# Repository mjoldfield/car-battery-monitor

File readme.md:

# Car battery monitor

My car tends to eat batteries! Sometimes, particularly during pandemic
summers many weeks pass without the car being used, and during this
time sometimes the battery discharges. I suspect the underlying
problem is that somewhere current is leaking to ground, but that seems
hard to fix. Instead, I’d be happy to just monitor the situation and
charge the battery if needed.

The car is usually parked in range of the home WiFi network, so a
convenient solution would be to have the car send me email about its
battery every once in while.

## code

All written in CircuitPython

## pcb

A PCB to hold tne TinyS2 and DC-DC converter boards, designed in KiCad.

## case

A 3D-printable case designed with OpenSCAD.

# Blog post

See [my blog](https://mjoldfield.com/atelier/2021/12/car-battery-monitor.html) for
more details.

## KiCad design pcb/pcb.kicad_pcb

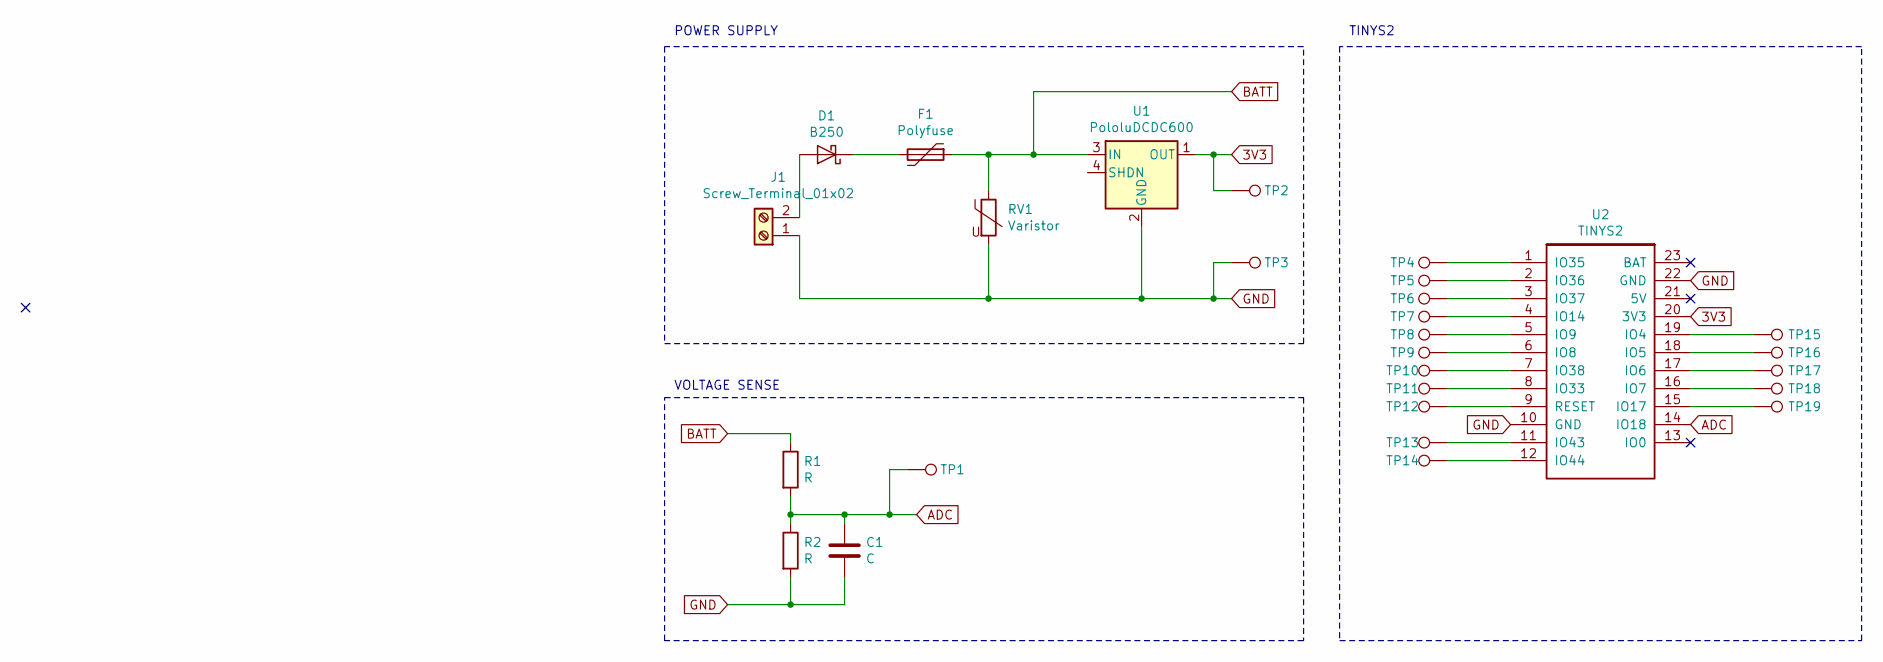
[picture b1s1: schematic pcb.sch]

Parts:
C1: C; C_0805_2012Metric_Pad1.15x1.40mm_HandSolder
D1: B250; D_SMB
F1: Polyfuse; C_1206_3216Metric_Pad1.42x1.75mm_HandSolder
J1: Screw_Terminal_01x02; TerminalBlock_bornier-2_P5.08mm
R1, R2: R; R_0805_2012Metric_Pad1.15x1.40mm_HandSolder
RV1: Varistor; C_1210_3225Metric_Pad1.42x2.65mm_HandSolder
TP1, TP2, TP3, TP4, TP5, TP6, TP7, TP8, TP9, TP10, TP11, TP12, TP13, TP14, TP15, TP16, TP17, TP18, TP19: TestPoint; TestPoint_THTPad_D2.0mm_Drill1.0mm
U1: PololuDCDC600; PololuDCDC4
U2: TINYS2

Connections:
3V3: TP2.1, U1.1 (OUT), U2.20 (3V3)
ADC: C1.1, R1.2, R2.1, TP1.1, U2.14 (IO18)
BATT: F1.1, R1.1, RV1.1, U1.3 (IN)
GND: C1.2, J1.1, R2.2, RV1.2, TP3.1, U1.2 (GND), U2.10 (GND), U2.22 (GND)
unnamed: D1.1 (K), F1.2
unnamed: D1.2 (A), J1.2
unnamed: TP4.1, U2.1 (IO35)
unnamed: TP5.1, U2.2 (IO36)
unnamed: TP6.1, U2.3 (IO37)
unnamed: TP7.1, U2.4 (IO14)
unnamed: TP8.1, U2.5 (IO9)
unnamed: TP9.1, U2.6 (IO8)
unnamed: TP10.1, U2.7 (IO38)
unnamed: TP11.1, U2.8 (IO33)
unnamed: TP12.1, U2.9 (RESET)
unnamed: TP13.1, U2.11 (IO43)
unnamed: TP14.1, U2.12 (IO44)
unnamed: TP15.1, U2.19 (IO4)
unnamed: TP16.1, U2.18 (IO5)
unnamed: TP17.1, U2.17 (IO6)
unnamed: TP18.1, U2.16 (IO7)
unnamed: TP19.1, U2.15 (IO17)

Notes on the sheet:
POWER SUPPLY
VOLTAGE SENSE
TINYS2

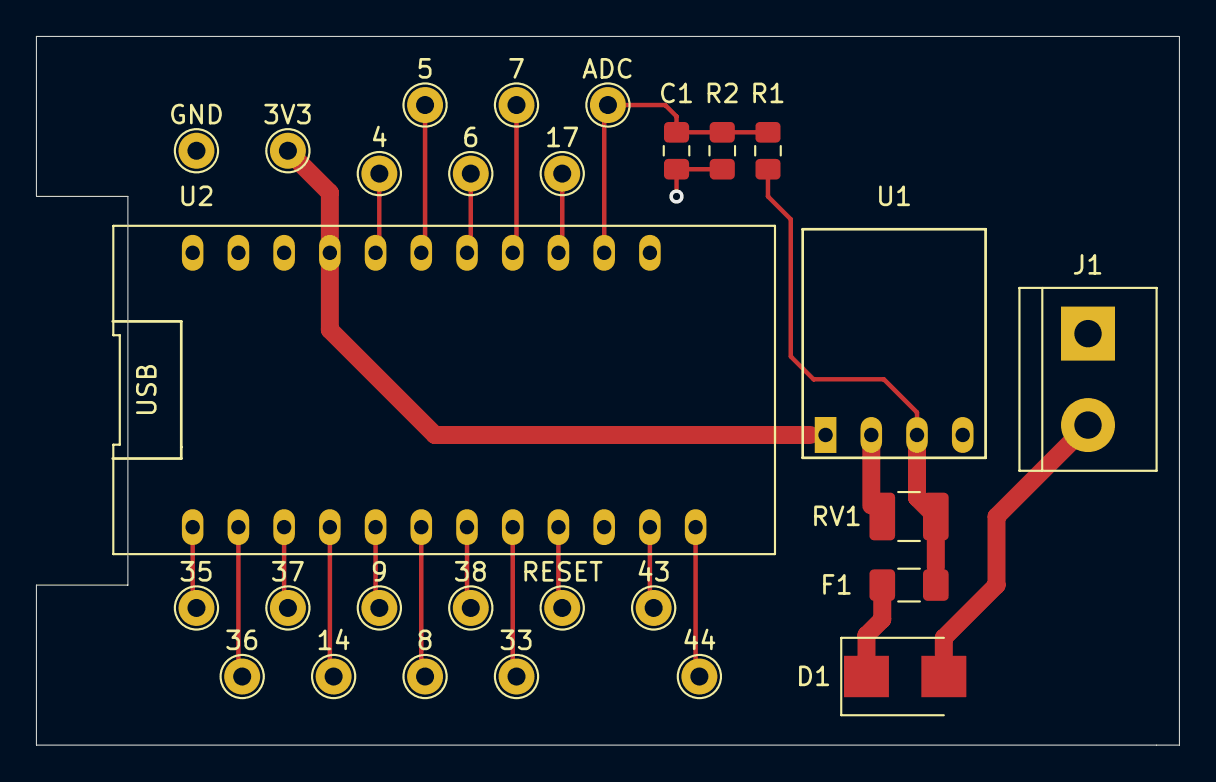
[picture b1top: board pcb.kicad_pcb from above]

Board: 2 copper layers, 63.5 x 39.4 mm, 28 parts (0 on the bottom side), 22 nets.

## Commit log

2021-12-17 First commit to public repo
2021-12-17 Added readme
2021-12-17 Fix link.
